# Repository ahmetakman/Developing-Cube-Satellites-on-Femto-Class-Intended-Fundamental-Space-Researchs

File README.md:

# Developing-Cube-Satellites-on-Femto-Class-Intended-Fundamental-Space-Researchs

The project won the second place in the coding category in the TUBITAK Inter-High School Research Projects Competition.
Project designed in Autodesk Eagle Pcb design program
#pasword for zip : licenced_design

Projenin Türkçe ismi "Temel Uzay Araştırmalarına Yönelik Femto Sınıfında Küp Uydu Geliştirilmesi"
Proje Tübitak Liseslerarası Araştırma Projeleri Yarışmasında kodlama dalında bölge ikinciliği aldı.
Proje Autodesk Eagle Pcb tasarım programında tasarlandı.
#zip dosyasının şifresi : licenced_design

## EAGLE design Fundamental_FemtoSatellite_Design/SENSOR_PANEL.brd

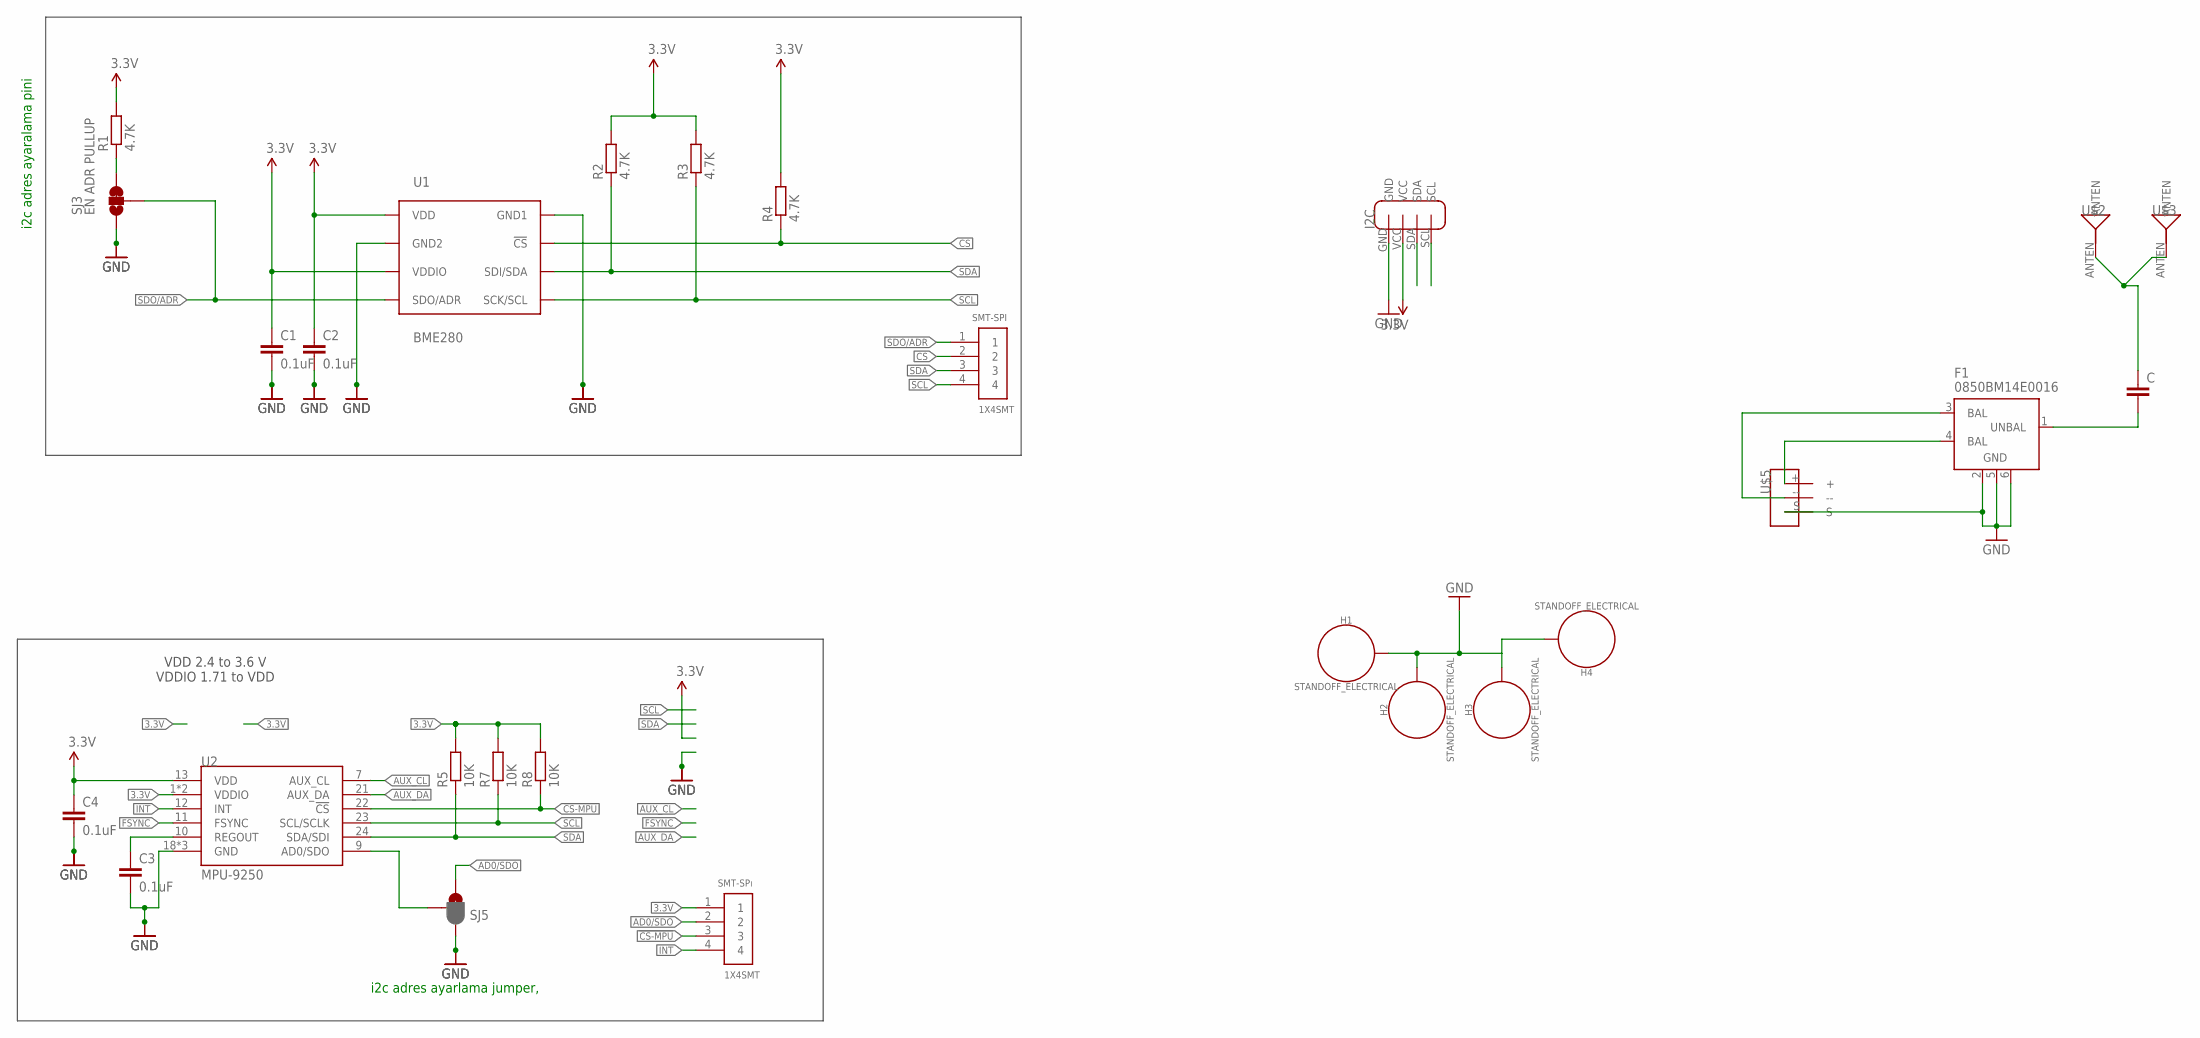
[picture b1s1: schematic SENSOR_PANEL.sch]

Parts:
C: C-EUC0805; C0805
C1, C2, C3, C4: 0.1uF; C0805
F1: 0850BM14E0016; 2450BM15A0002
H1, H2, H3, H4: STANDOFF_ELECTRICAL; STANDOFF-ELECTRICAL
R1, R2, R3, R4: 4.7K; R0805
R5, R7, R8: 10K; R0805
SJ3: EN ADR PULLUP; PAD-JUMPER-3-2OF3_NC_BY_TRACE_YES_SILK_FULL_BOX
SJ5: JUMPER_PAD-3-1&2_NC_BY_PASTE; PAD-HUMPER-3-1&2_NC_BY_PASTE_YES_SILK_FULL_BOX
SMT-SPI: 1X4SMT; 1X4-SMT
SMT-SPı: 1X4SMT; 1X4-SMT
U1: BME280; BME280_LGA
U2: MPU-9250; QFN24_PAD
U$1: I2C
U$2, U$3: ANTEN
U$5: 3PINSENSOR

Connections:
3.3V: C1.1, C2.1, C4.1, R1.2, R2.2, R3.2, R4.2, R5.2, R7.2, R8.2, SMT-SPı.1, U1.P$6 (VDDIO), U1.P$8 (VDD), U2.1 (VDDIO), U2.8 (VDDIO), U2.13 (VDD), U$1.VCC
!CS-MPU: R8.1, SMT-SPı.3, U2.22 (!CS)
AD0/SDO: SJ5.3, SMT-SPı.2
ADSD_STUB: SJ5.2, U2.9 (AD0/SDO)
AUX_CL: U2.7 (AUX_CL)
AUX_DA: U2.21 (AUX_DA)
CS: R4.1, SMT-SPI.2, U1.P$2 (!CS)
FSYNC: U2.11 (FSYNC)
GND: C1.2, C2.2, C3.2, C4.2, F1.2 (GND), F1.5 (GND), F1.6 (GND), H1.P1, H2.P1, H3.P1, H4.P1, SJ3.1, SJ5.1, U1.P$1 (GND1), U1.P$7 (GND2), U2.18 (GND), U2.20 (GND), U2.CENTER (GND), U$1.GND, U$5.S
INT: SMT-SPı.4, U2.12 (INT)
unnamed: C.2, F1.1 (UNBAL)
unnamed: R1.1, SJ3.3
unnamed: C.1, U$2.ANTEN, U$3.ANTEN
unnamed: F1.3 (BAL), U$5.--
unnamed: F1.4 (BAL), U$5.+
REGOUT: C3.1, U2.10 (REGOUT)
SCL: R3.1, R7.1, SMT-SPI.4, U1.P$4 (SCK/SCL), U2.23 (SCL/SCLK), U$1.SCL
SDA: R2.1, R5.1, SMT-SPI.3, U1.P$3 (SDI/SDA), U2.24 (SDA/SDI), U$1.SDA
SDO/ADR: SJ3.2, SMT-SPI.1, U1.P$5 (SDO/ADR)

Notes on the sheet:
VDD 2.4 to 3.6 V VDDIO 1.71 to VDD
i2c adres ayaralama pini
i2c adres ayarlama jumper,

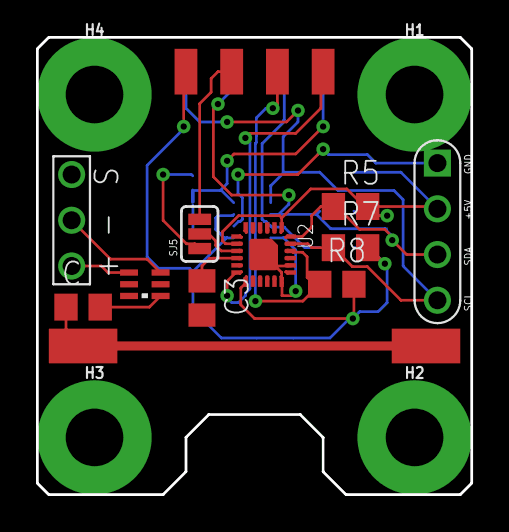
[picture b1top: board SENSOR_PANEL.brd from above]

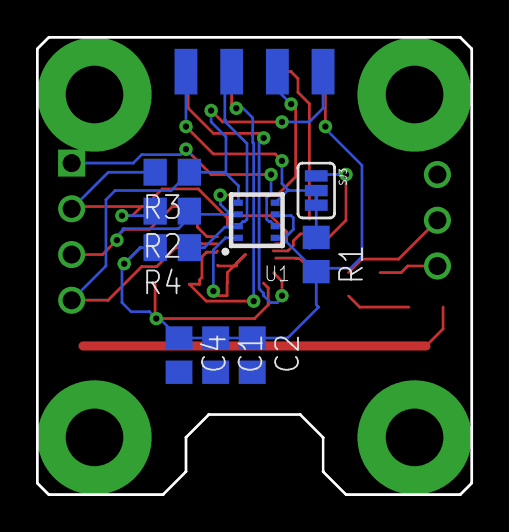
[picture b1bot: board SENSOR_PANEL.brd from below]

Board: 2 copper layers, 24.1 x 25.4 mm, 27 parts (10 on the bottom side), 16 nets.

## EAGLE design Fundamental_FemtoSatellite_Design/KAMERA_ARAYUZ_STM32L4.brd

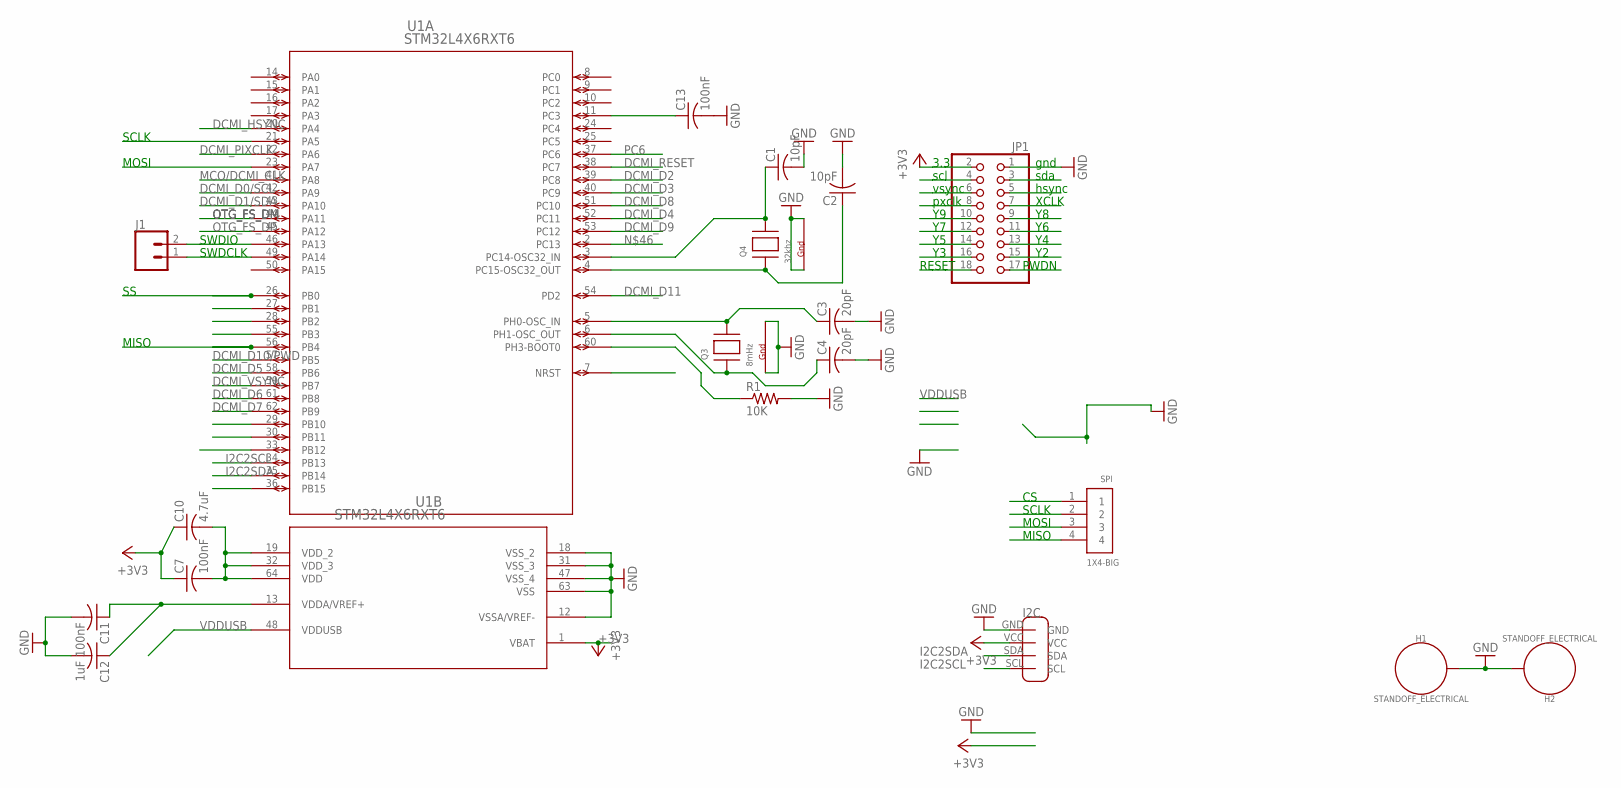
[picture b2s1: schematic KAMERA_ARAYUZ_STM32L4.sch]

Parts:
C1, C2: 10pF; C0805
C3, C4: 20pF; C0805
C7, C11, C13: 100nF; C0805
C10: 4.7uF; C0805
C12: 1uF; C0805
H1, H2: STANDOFF_ELECTRICAL; STANDOFF-ELECTRICAL
J1: CONN_02; 1X02
JP1: PINHD-2X9-CBIG; 2X09-CLEANBIG
Q3: 8mHz; NX3225
Q4: 32khz; NX3225
R1: 10K; R0805
SPI: 1X4-BIG; 1X04-BIG
U1: STM32L4X6RXT6; LQFP64-10X10MM
U$2: I2C

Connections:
+3V3: C7.1, C10.1, JP1.2, U1.1 (VBAT), U$2.VCC
CS: SPI.1, U1.26 (PB0)
DCMI_D0/SCL: JP1.4, U1.42 (PA9)
DCMI_D1/SDA: JP1.3, U1.43 (PA10)
DCMI_D2: JP1.15, U1.39 (PC8)
DCMI_D3: JP1.16, U1.40 (PC9)
DCMI_D4: JP1.13, U1.52 (PC11)
DCMI_D5: JP1.14, U1.58 (PB6)
DCMI_D6: JP1.11, U1.61 (PB8)
DCMI_D7: JP1.12, U1.62 (PB9)
DCMI_D8: JP1.9, U1.51 (PC10)
DCMI_D9: JP1.10, U1.53 (PC12)
DCMI_D10/PWD: JP1.17, U1.57 (PB5)
DCMI_D11: U1.54 (PD2)
DCMI_HSYNC: JP1.5, U1.20 (PA4)
DCMI_PIXCLK: JP1.8, U1.22 (PA6)
DCMI_RESET: JP1.18, U1.38 (PC7)
DCMI_VSYNC: JP1.6, U1.59 (PB7)
GND: C1.2, C2.2, C3.2, C4.2, C11.2, C12.2, C13.2, H1.P1, H2.P1, JP1.1, Q3.2 (G2), Q3.4 (G1), Q4.2 (G2), Q4.4 (G1), R1.2, U1.12 (VSSA/VREF-), U1.18 (VSS_2), U1.31 (VSS_3), U1.47 (VSS_4), U1.63 (VSS), U$2.GND
I2C2SCL: U1.34 (PB13), U$2.SCL
I2C2SDA: U1.35 (PB14), U$2.SDA
MCO/DCMI_CLK: JP1.7, U1.41 (PA8)
MISO: SPI.4, U1.56 (PB4)
MOSI: SPI.3, U1.23 (PA7)
unnamed: C2.1, Q4.1 (X1), U1.4 (PC15-OSC32_OUT)
unnamed: C3.1, Q3.3 (X2), U1.5 (PH0-OSC_IN)
unnamed: C4.1, Q3.1 (X1), U1.6 (PH1-OSC_OUT)
unnamed: R1.1, U1.60 (PH3-BOOT0)
unnamed: C11.1, C12.1, U1.13 (VDDA/VREF+)
unnamed: C13.1, U1.11 (PC3)
unnamed: C7.2, C10.2, U1.19 (VDD_2), U1.32 (VDD_3), U1.64 (VDD)
unnamed: C1.1, Q4.3 (X2), U1.3 (PC14-OSC32_IN)
OTG_FS_DM: U1.44 (PA11)
OTG_FS_DP: U1.45 (PA12)
PC6: U1.37 (PC6)
SCLK: SPI.2, U1.21 (PA5)
SWDCLK: J1.1, U1.49 (PA14)
SWDIO: J1.2, U1.46 (PA13)
VDDUSB: U1.48 (VDDUSB)

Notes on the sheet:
3.3
scl
vsync
pxclk
RESET
PWDN
XCLK
hsync
sda
gnd
SWDIO
SWDCLK
MISO
MOSI
SCLK

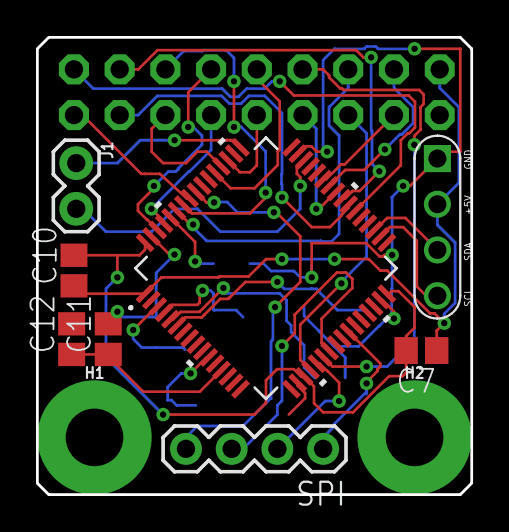
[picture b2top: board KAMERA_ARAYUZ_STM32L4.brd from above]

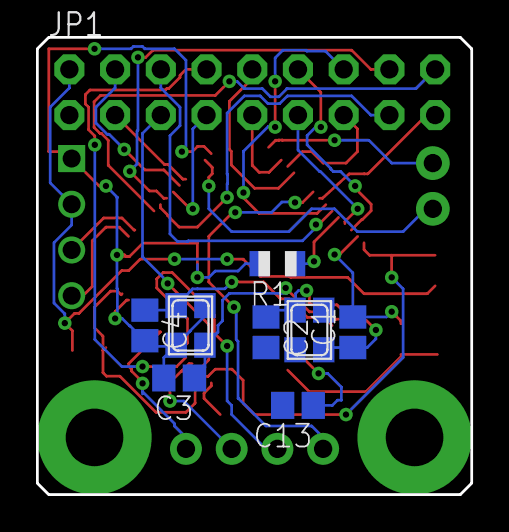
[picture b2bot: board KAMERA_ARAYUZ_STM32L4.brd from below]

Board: 2 copper layers, 24.1 x 25.4 mm, 19 parts (9 on the bottom side), 34 nets.

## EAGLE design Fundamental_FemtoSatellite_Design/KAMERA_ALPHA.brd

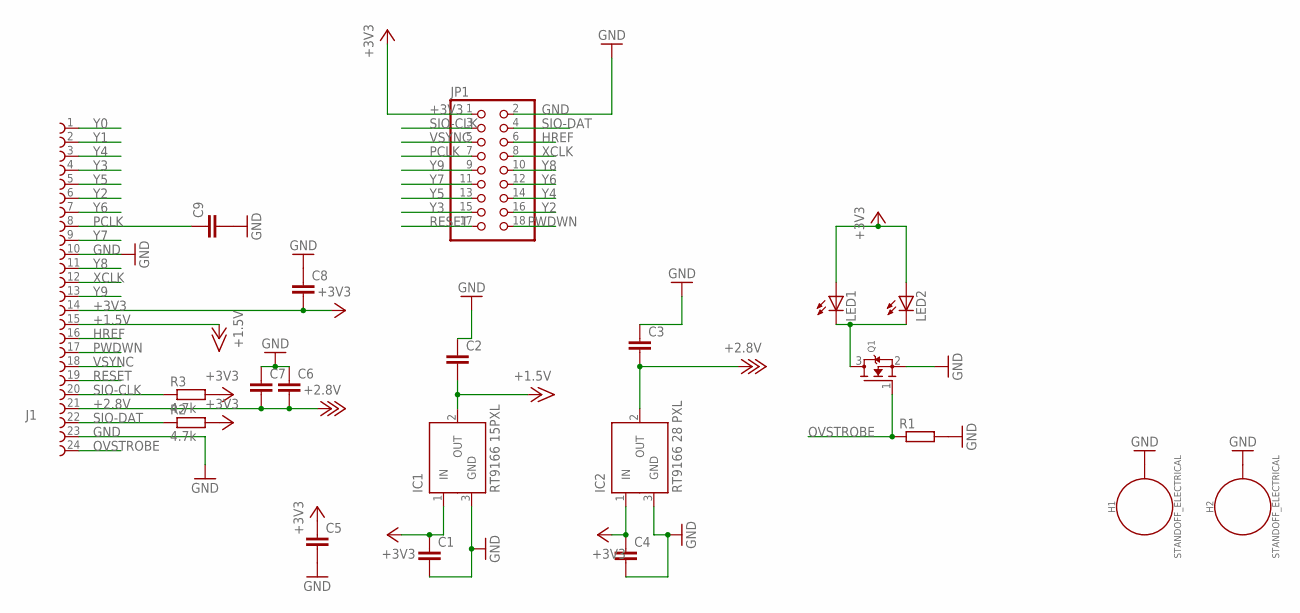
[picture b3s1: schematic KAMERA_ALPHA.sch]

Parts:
C1, C2, C3, C4, C5, C6, C7, C8, C9: C-EUC0805K; C0805K
H1, H2: STANDOFF_ELECTRICAL; STANDOFF-ELECTRICAL
IC1: RT9166 15PXL; SOT23
IC2: RT9166 28 PXL; SOT23
J1: 68712414022
JP1: PINHD-2X9; 2X09
LED1, LED2: LEDCHIPLED_0805; CHIPLED_0805
Q1: MOSFET-NREFLOW; SOT23
R1: R-EU_R0805; R0805
R2, R3: 4.7k; R0805

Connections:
+1.5V: C2.2, IC1.2 (OUT), J1.15 (10)
+2.8V: C3.2, C6.2, C7.2, IC2.2 (OUT), J1.21 (4)
+3V3: C1.1, C4.1, C5.1, C8.2, IC1.1 (IN), IC2.1 (IN), J1.14 (11), JP1.1, LED1.A, LED2.A, R2.2, R3.2
GND: C1.2, C2.1, C3.1, C4.2, C5.2, C6.1, C7.1, C8.1, C9.2, H1.P1, H2.P1, IC1.3 (GND), IC2.3 (GND), J1.10 (15), J1.23 (2), JP1.2, Q1.2 (S), R1.2
HREF: J1.16 (9), JP1.6
unnamed: LED1.C, LED2.C, Q1.3 (D)
OVSTROBE: J1.24 (1), Q1.1 (G), R1.1
PCLK: C9.1, J1.8 (17), JP1.7
PWDWN: J1.17 (8), JP1.18
RESET: J1.19 (6), JP1.17
SIO-CLK: J1.20 (5), JP1.3, R3.1
SIO-DAT: J1.22 (3), JP1.4, R2.1
VSYNC: J1.18 (7), JP1.5
XCLK: J1.12 (13), JP1.8
Y0: J1.1 (24)
Y1: J1.2 (23)
Y2: J1.6 (19), JP1.16
Y3: J1.4 (21), JP1.15
Y4: J1.3 (22), JP1.14
Y5: J1.5 (20), JP1.13
Y6: J1.7 (18), JP1.12
Y7: J1.9 (16), JP1.11
Y8: J1.11 (14), JP1.10
Y9: J1.13 (12), JP1.9

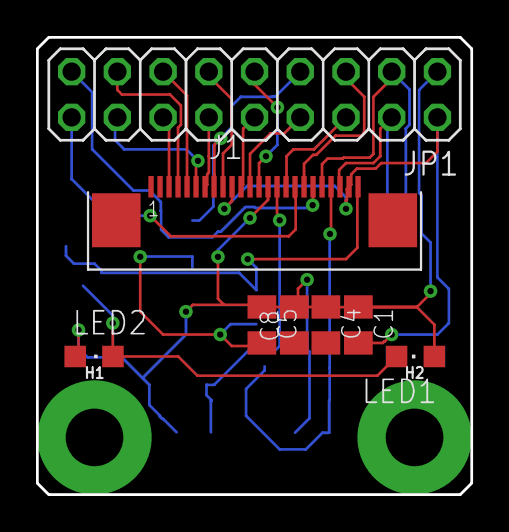
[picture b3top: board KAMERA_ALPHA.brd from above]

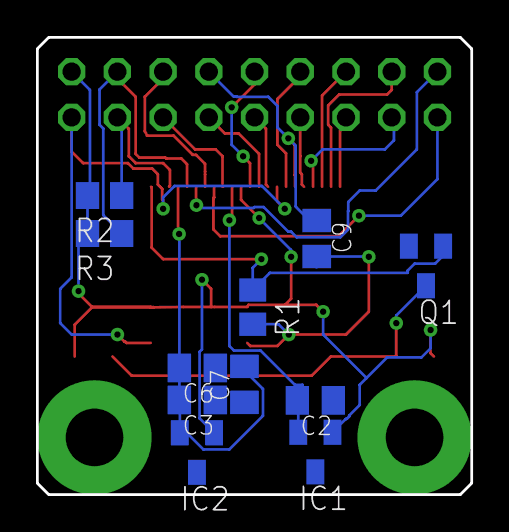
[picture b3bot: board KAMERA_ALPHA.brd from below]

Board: 2 copper layers, 24.1 x 25.4 mm, 21 parts (11 on the bottom side), 22 nets.

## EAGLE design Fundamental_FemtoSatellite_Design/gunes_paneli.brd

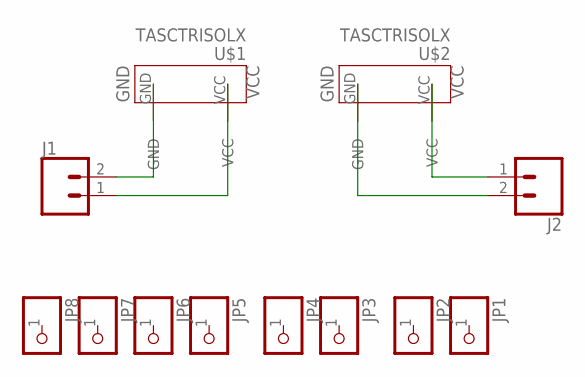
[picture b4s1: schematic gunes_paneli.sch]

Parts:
J1, J2: CONN_02; 1X02
JP1, JP2, JP3, JP4, JP5, JP6, JP7, JP8: PINHD-1X1CB; 1X01-CLEANBIG
U$1, U$2: TASCTRISOLX; TASCTRİSOLX

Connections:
unnamed: J1.2, U$1.GND
unnamed: J1.1, U$1.VCC
unnamed: J2.1, U$2.VCC
unnamed: J2.2, U$2.GND

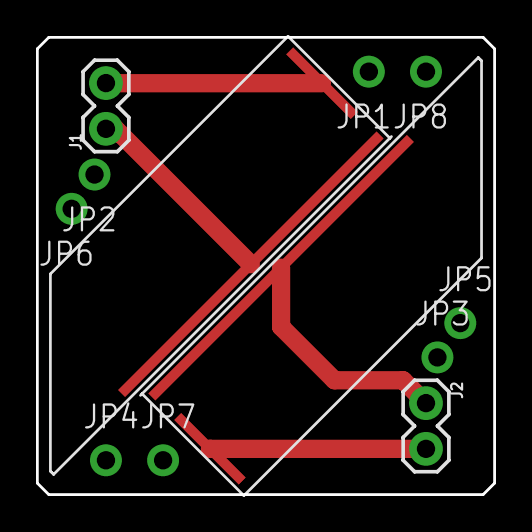
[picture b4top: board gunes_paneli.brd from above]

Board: 2 copper layers, 25.4 x 25.4 mm, 12 parts (0 on the bottom side), 4 nets.

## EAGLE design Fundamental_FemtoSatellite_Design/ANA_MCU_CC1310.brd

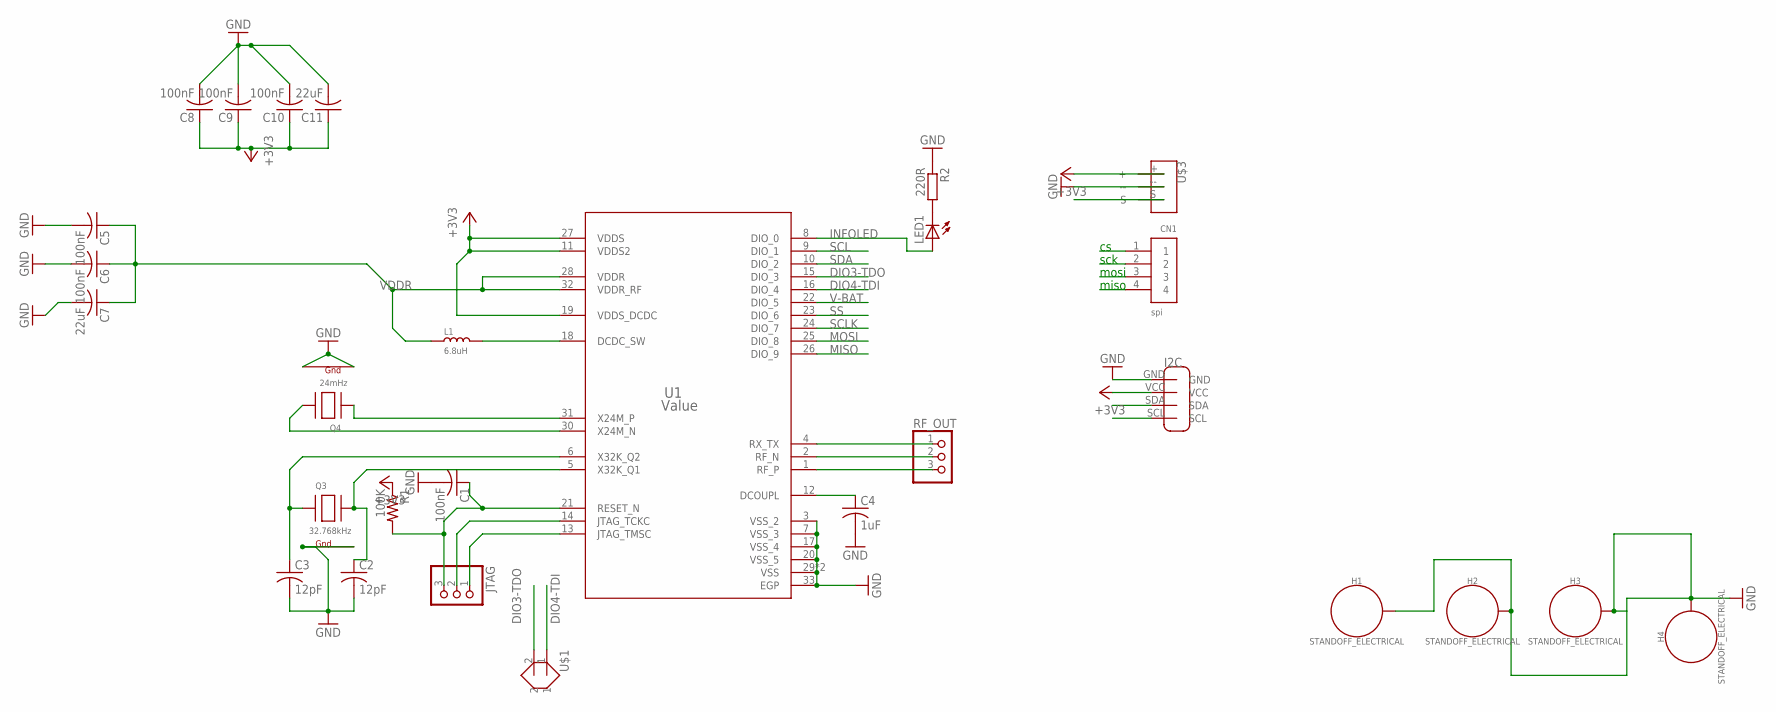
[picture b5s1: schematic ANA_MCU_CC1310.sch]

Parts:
C1, C5, C6, C8, C9, C10: 100nF; C0805K
C2, C3: 12pF; C0805K
C4: 1uF; C0805K
C7, C11: 22uF; C0805K
CN1: spi; 1X04-CLEANBIG
H1, H2, H3, H4: STANDOFF_ELECTRICAL; STANDOFF-ELECTRICAL
JTAG: PINHD-1X3CB; 1X03-CLEANBIG
L1: 6.8uH; L0805
LED1: LEDCHIP-LED0805; CHIP-LED0805
Q3: 32.768kHz; NX3225
Q4: 24mHz; NX3225
R1: 100K; R0805
R2: 220R; R0805
RF_OUT: PINHD-1X3CB; 1X03-CLEANBIG
U1: Value; RSM0032B
U$1: DCMOTOR
U$2: I2C
U$3: 3PINSENSOR

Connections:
+3V3: C8.1, C9.1, C10.1, C11.1, R1.1, U1.11 (VDDS2), U1.19 (VDDS_DCDC), U1.27 (VDDS), U$2.VCC, U$3.+
DIO3-TDO: U1.15 (DIO_3), U$1.2
DIO4-TDI: U1.16 (DIO_4), U$1.1
GND: C1.2, C2.2, C3.2, C4.2, C5.2, C6.2, C7.2, C8.2, C9.2, C10.2, C11.2, H1.P1, H2.P1, H3.P1, H4.P1, Q3.2 (G2), Q3.4 (G1), Q4.2 (G2), Q4.4 (G1), R2.1, U1.3 (VSS_2), U1.7 (VSS_3), U1.17 (VSS_4), U1.20 (VSS_5), U1.29 (VSS), U1.33 (EGP), U1.V (VSS), U$2.GND, U$3.--
INFOLED: LED1.A, U1.8 (DIO_0)
MISO: CN1.4, U1.26 (DIO_9)
MOSI: CN1.3, U1.25 (DIO_8)
unnamed: Q4.3 (X2), U1.30 (X24M_N)
unnamed: C3.1, Q3.1 (X1), U1.6 (X32K_Q2)
unnamed: Q4.1 (X1), U1.31 (X24M_P)
unnamed: LED1.C, R2.2
unnamed: L1.2, U1.18 (DCDC_SW)
unnamed: C2.1, Q3.3 (X2), U1.5 (X32K_Q1)
unnamed: C1.1, JTAG.3, R1.2, U1.21 (RESET_N)
unnamed: JTAG.2, U1.14 (JTAG_TCKC)
unnamed: JTAG.1, U1.13 (JTAG_TMSC)
unnamed: C4.1, U1.12 (DCOUPL)
unnamed: RF_OUT.3, U1.1 (RF_P)
unnamed: RF_OUT.2, U1.2 (RF_N)
unnamed: RF_OUT.1, U1.4 (RX_TX)
SCL: U1.9 (DIO_1), U$2.SCL
SCLK: CN1.2, U1.24 (DIO_7)
SDA: U1.10 (DIO_2), U$2.SDA
SS: CN1.1, U1.23 (DIO_6)
V-BAT: U1.22 (DIO_5), U$3.S
VDDR: C5.1, C6.1, C7.1, L1.1, U1.28 (VDDR), U1.32 (VDDR_RF)

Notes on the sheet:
sck
mosi
miso

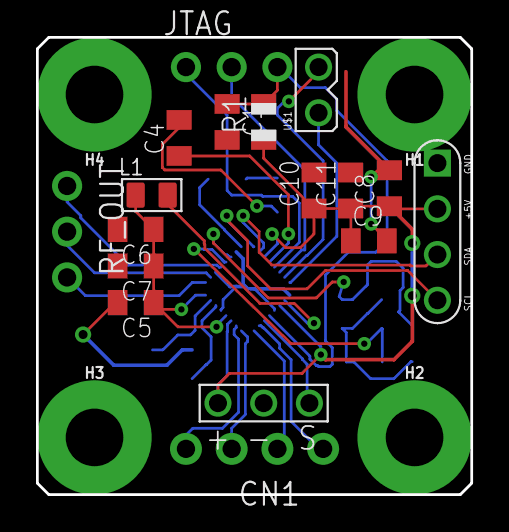
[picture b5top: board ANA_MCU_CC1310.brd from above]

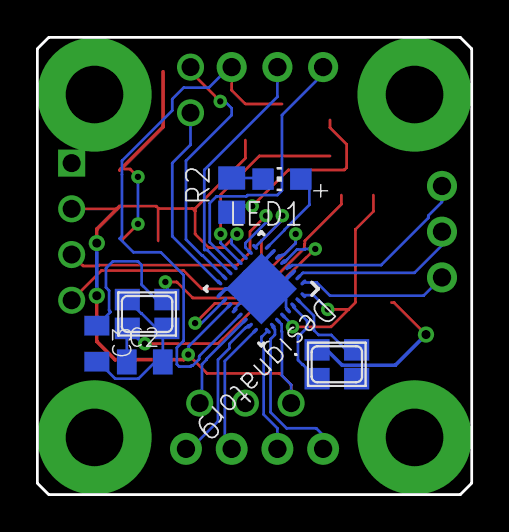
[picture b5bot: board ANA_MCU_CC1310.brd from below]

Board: 2 copper layers, 24.1 x 25.4 mm, 28 parts (7 on the bottom side), 26 nets.

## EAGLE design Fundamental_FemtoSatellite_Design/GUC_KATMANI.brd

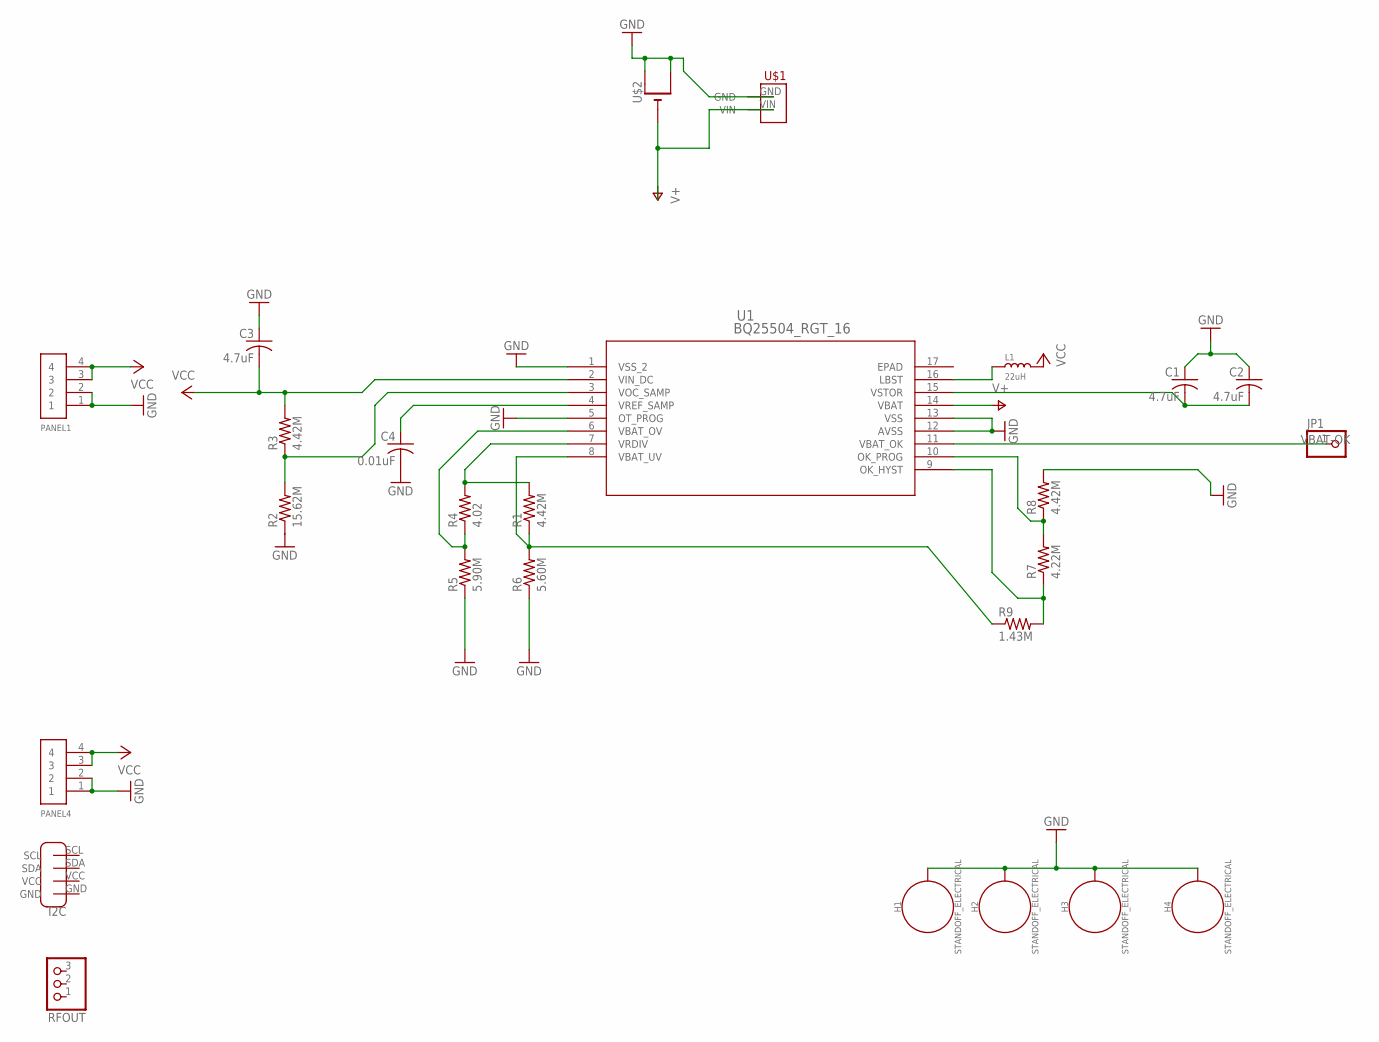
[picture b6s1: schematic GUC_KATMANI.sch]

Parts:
C1, C2, C3: 4.7uF; C0805K
C4: 0.01uF; C0805K
H1, H2, H3, H4: STANDOFF_ELECTRICAL; STANDOFF-ELECTRICAL
JP1: PINHD-1X1CB; 1X01-CLEANBIG
L1: 22uH; L0805
PANEL1, PANEL4: 1X4-CLEANBIG; 1X04-CLEANBIG
R1, R3, R8: 4.42M; R0805
R2: 15.62M; R0805
R4: 4.02; R0805
R5: 5.90M; R0805
R6: 5.60M; R0805
R7: 4.22M; R0805
R9: 1.43M; R0805
RFOUT: PINHD-1X3CB; 1X03-CLEANBIG
U1: BQ25504_RGT_16; RGT16_1P7X1P7
U$1: 2PINKLEMENS
U$2: CR1220SMT; CR1220-SMD
U$3: I2C

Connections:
EPAD: U1.17 (EPAD)
GND: C1.1, C2.1, C3.1, C4.2, H1.P1, H2.P1, H3.P1, H4.P1, PANEL1.1, PANEL1.2, PANEL4.1, PANEL4.2, R2.1, R5.1, R6.1, R8.2, U1.1 (VSS_2), U1.5 (OT_PROG), U1.12 (AVSS), U1.13 (VSS), U$1.GND, U$2.+$1 (+), U$2.+$2 (+1)
unnamed: R2.2, R3.1, U1.3 (VOC_SAMP)
unnamed: C4.1, U1.4 (VREF_SAMP)
unnamed: R4.1, R5.2, U1.6 (VBAT_OV)
unnamed: R1.2, R4.2, U1.7 (VRDIV)
unnamed: R1.1, R6.2, R9.1, U1.8 (VBAT_UV)
unnamed: R7.2, R8.1, U1.10 (OK_PROG)
unnamed: L1.1, U1.16 (LBST)
unnamed: R7.1, R9.2, U1.9 (OK_HYST)
unnamed: C1.2, C2.2, U1.15 (VSTOR)
V+: U1.14 (VBAT), U$1.VIN, U$2.-
VBAT-OK: JP1.1, U1.11 (VBAT_OK)
VCC: C3.2, L1.2, PANEL1.3, PANEL1.4, PANEL4.3, PANEL4.4, R3.2, U1.2 (VIN_DC)

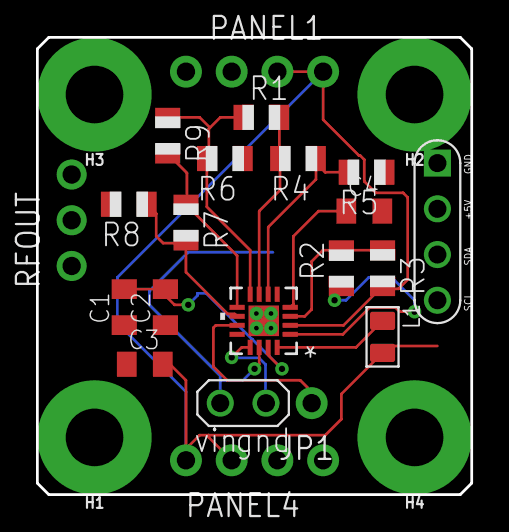
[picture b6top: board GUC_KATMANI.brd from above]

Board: 2 copper layers, 24.1 x 25.4 mm, 26 parts (1 on the bottom side), 13 nets.

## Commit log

2019-08-06 Eagle Pcb--------- password zip = licenced_design
2019-08-06 main report with english titles
2019-08-06 project summary - ENG
2019-08-06 Birleştirilimiş Proje Dökümanları
2019-08-06 ProjectSummaryEng

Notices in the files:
parts and their libraries:
SparkFun-Hardware: Licensing: Creative Commons ShareAlike 4.0 International - https://creativecommons.org/licenses/by-sa/4.0
Wurth_Elektronik_Electromechanic_FPC_Con: Copyright: Würth Elektronik
COPYRIGHT: Copyright C 2016 Accelerated Designs. All rights reserved
